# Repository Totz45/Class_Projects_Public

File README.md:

# Class_Projects_Public
This repository serves as all of the coding classwork I have done in college. For recruiters view only.

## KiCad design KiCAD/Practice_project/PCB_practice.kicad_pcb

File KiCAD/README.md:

# KiCAD Project
The project located in this directory was done outside of academic projects and accomplished during June 2025.

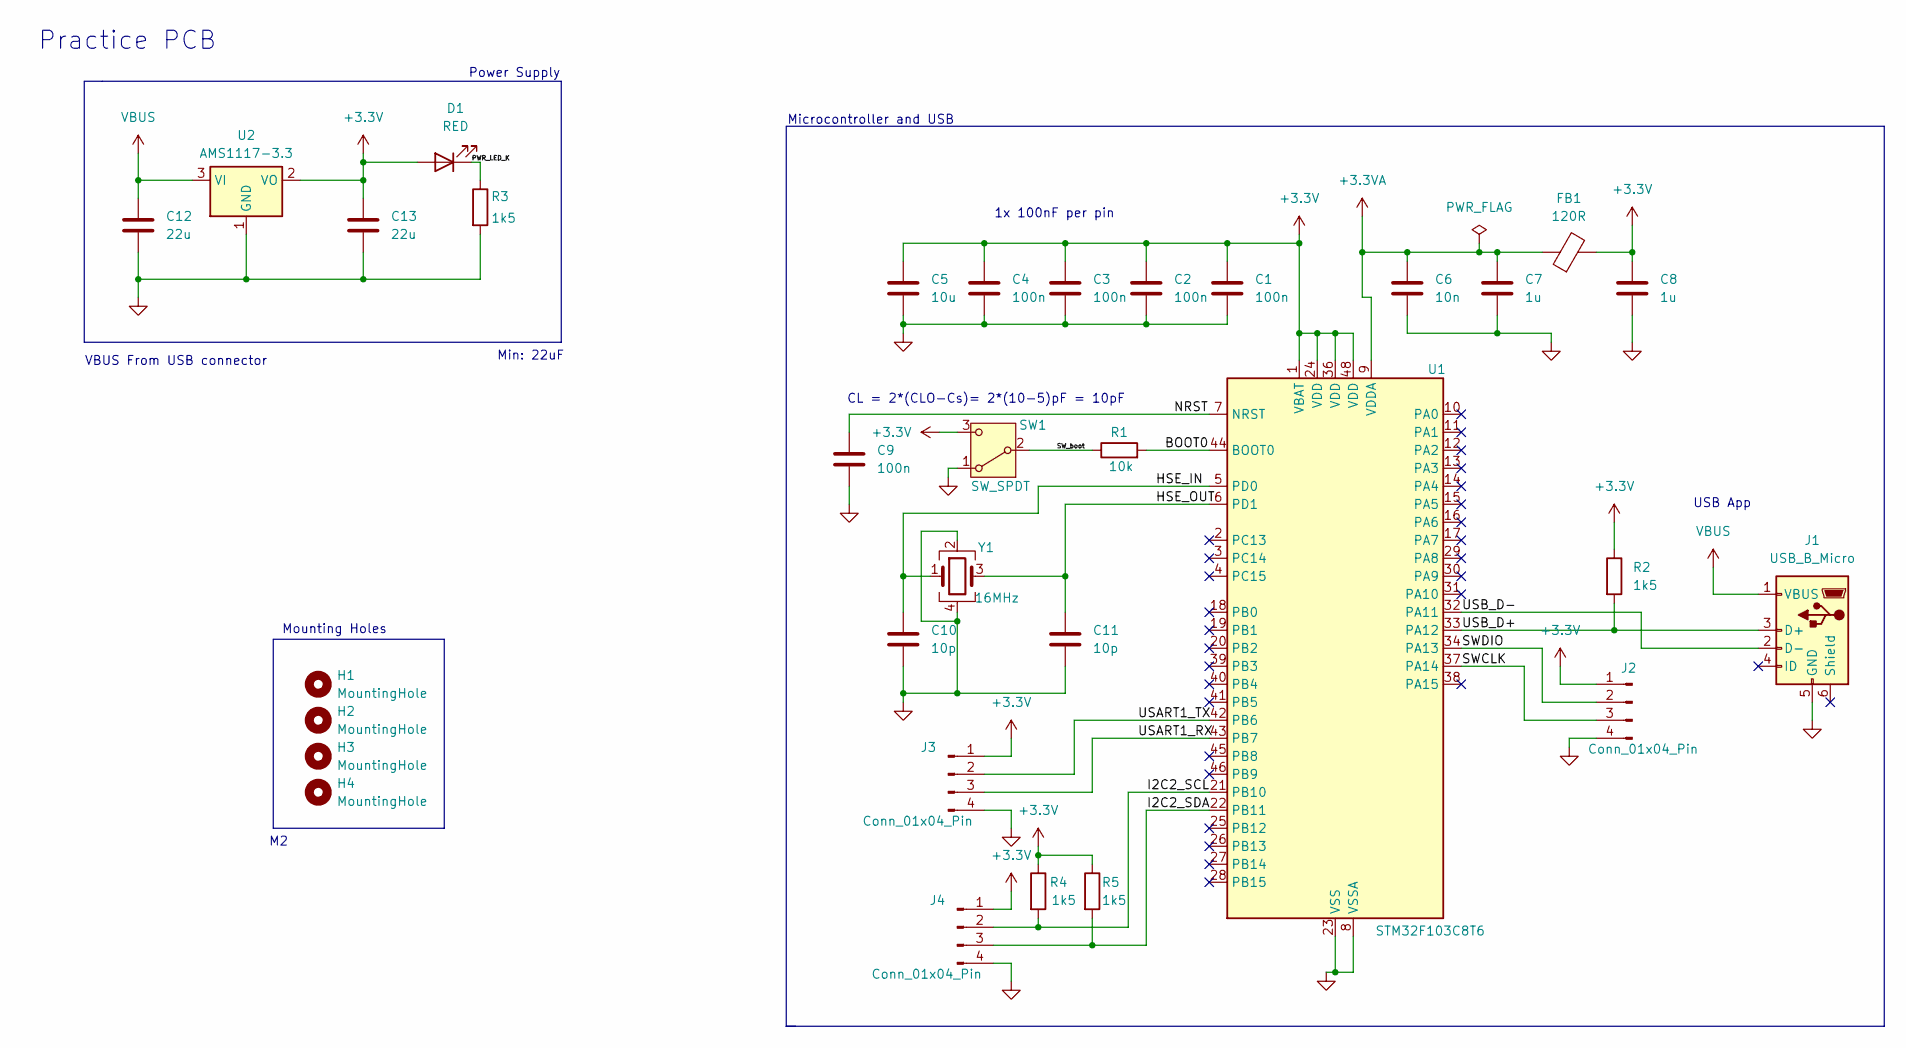
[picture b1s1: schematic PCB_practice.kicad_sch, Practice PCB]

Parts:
C1, C2, C3, C4, C9: 100n; C_0402_1005Metric
C5: 10u; C_0603_1608Metric
C6: 10n; C_0402_1005Metric
C7, C8: 1u; C_0402_1005Metric
C10, C11: 10p; C_0402_1005Metric
C12, C13: 22u; C_0805_2012Metric
D1: RED; LED_0603_1608Metric
FB1: 120R; L_0603_1608Metric
H1, H2, H3, H4: MountingHole; MountingHole_2.2mm_M2
J1: USB_B_Micro; USB_Micro-B_Wuerth_629105150521
J2, J3, J4: Conn_01x04_Pin; PinHeader_1x04_P2.54mm_Vertical
R1: 10k; R_0402_1005Metric
R2, R3, R4, R5: 1k5; R_0402_1005Metric
SW1: SW_SPDT; SW_SPDT_PCM12
U1: STM32F103C8T6; LQFP-48_7x7mm_P0.5mm
U2: AMS1117-3.3; SOT-223-3_TabPin2
Y1: 16MHz; Crystal_SMD_3225-4Pin_3.2x2.5mm

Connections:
+3.3V: C1.1, C2.1, C3.1, C4.1, C5.1, C8.1, C13.1, D1.2 (A), FB1.2, J2.1, J3.1, J4.1, R2.1, R4.1, R5.1, SW1.3 (C), U1.1 (VBAT), U1.24 (VDD), U1.36 (VDD), U1.48 (VDD), U2.2 (VO)
+3.3VA: C6.1, C7.1, FB1.1, U1.9 (VDDA)
/BOOT0: R1.2, U1.44 (BOOT0)
/HSE_IN: C10.1, U1.5 (PD0), Y1.1
/HSE_OUT: C11.1, U1.6 (PD1), Y1.3
/I2C2_SCL: J4.2, R4.2, U1.21 (PB10)
/I2C2_SDA: J4.3, R5.2, U1.22 (PB11)
/NRST: C9.1, U1.7 (NRST)
/PWR_LED_K: D1.1 (K), R3.1
/SWCLK: J2.3, U1.37 (PA14)
/SWDIO: J2.2, U1.34 (PA13)
/SW_boot: R1.1, SW1.2 (B)
/USART1_RX: J3.3, U1.43 (PB7)
/USART1_TX: J3.2, U1.42 (PB6)
/USB_D+: J1.3 (D+), R2.2, U1.33 (PA12)
/USB_D-: J1.2 (D-), U1.32 (PA11)
GND: C1.2, C2.2, C3.2, C4.2, C5.2, C6.2, C7.2, C8.2, C9.2, C10.2, C11.2, C12.2, C13.2, J1.5 (GND), J2.4, J3.4, J4.4, R3.2, SW1.1 (A), U1.8 (VSSA), U1.23 (VSS), U1.35 (VSS), U1.47 (VSS), U2.1 (GND), Y1.2, Y1.4
VBUS: C12.1, J1.1 (VBUS), U2.3 (VI)

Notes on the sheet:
1x 100nF per pin
VBUS From USB connector
Min: 22uF
USB App
Microcontroller and USB
Power Supply
CL = 2*(CLO-Cs)= 2*(10-5)pF = 10pF
Practice PCB
Mounting Holes

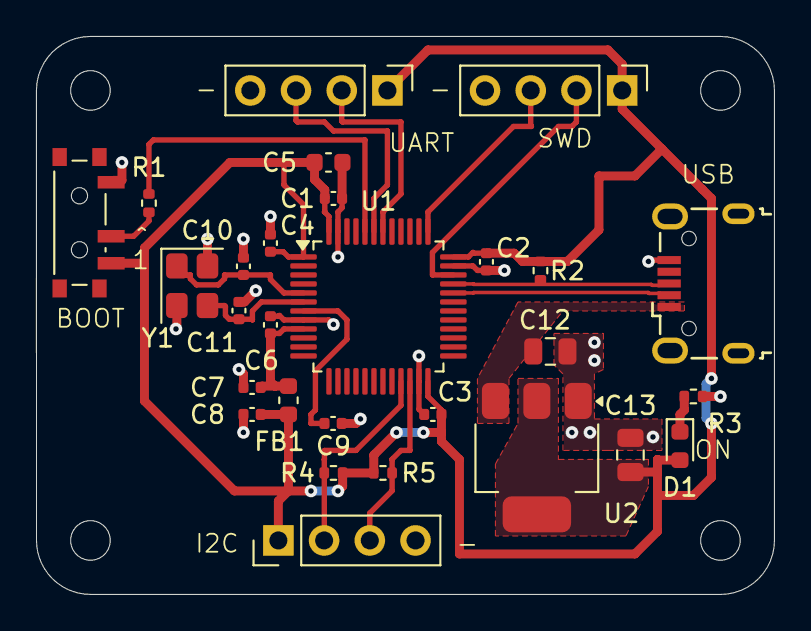
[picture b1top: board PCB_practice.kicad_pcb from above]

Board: 2 copper layers, 41.0 x 31.0 mm, 32 parts (0 on the bottom side), 18 nets.

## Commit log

2025-08-13 Uploaded Classwork
    This is all the classwork done at Tennessee Tech as a part of its Electrical and Computer Engineering Curriculum.
2025-08-13 Rearranged and removed unrelated files
2025-08-15 Included Microcomputer Projects
    Includes both C and assembly code.
2025-08-15 Included Matlab Projects
2025-08-18 Deleted Notes on Public Profile
2025-08-18 Delete How to CSC2510.png
    Removed screenshots
2025-08-26 Removed reference programs
    These programs were given to me to reference when coding in C++.
2025-08-26 Added SPICE and Digital Projects
    View Read ME of the digital software to access .dig files.
2025-08-26 Added KiCAD side project
    I decided to pursue a side project after college to upskill myself in printed circuit board design.
2025-09-24 Improved CSC1300 Programs
    Debugged Array access errors in program 4, improved clarity in Program 1.
2025-09-24 Removed outdated code in Capstone project
    Capstone Project code is not up to date with finished product code.
2025-09-24 Included time frames
    Made it clear when each project was completed.
